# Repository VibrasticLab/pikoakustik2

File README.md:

# Pikoakustik V2

This is audiometri tool project (still in heavy development).
Main chip are STM32F4 and Audio-DAC MAX98357A.

If need previous works, see here: [Pikoakustik](https://github.com/VibrasticLab/pikoakustik)

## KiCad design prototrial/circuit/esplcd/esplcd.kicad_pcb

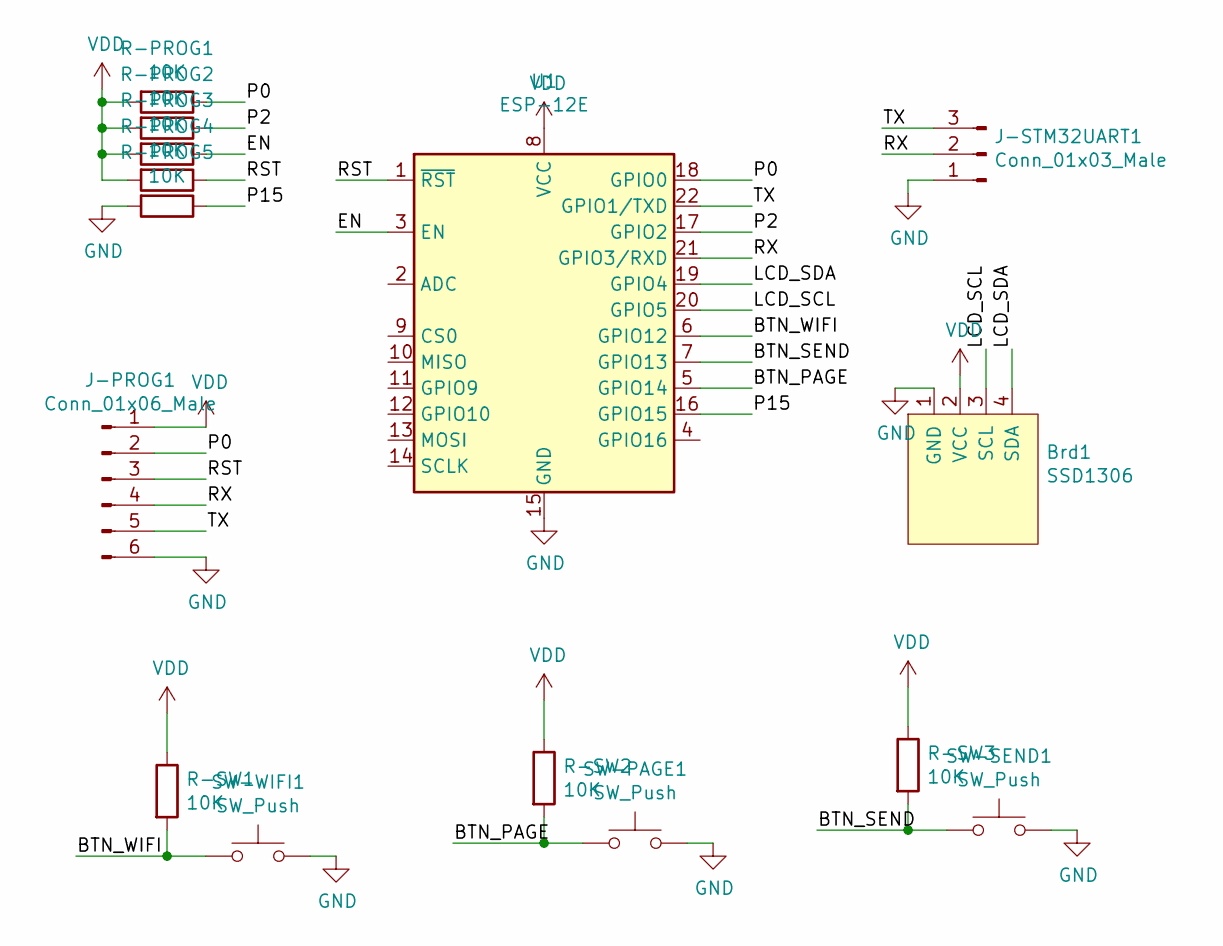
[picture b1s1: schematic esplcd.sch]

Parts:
Brd1: SSD1306; 128x64OLED
J-PROG1: Conn_01x06_Male; PinHeader_1x06_P2.54mm_Vertical
J-STM32UART1: Conn_01x03_Male; Molex_KK-254_AE-6410-03A_1x03_P2.54mm_Vertical
R-PROG1, R-PROG2, R-PROG3, R-PROG4, R-PROG5: 10K; R_0805_2012Metric_Pad1.20x1.40mm_HandSolder
R-SW1, R-SW2, R-SW3: 10K; R_0805_2012Metric_Pad1.20x1.40mm_HandSolder
SW-PAGE1: SW_Push; SW_PUSH_6mm
SW-SEND1: SW_Push; SW_PUSH_6mm
SW-WIFI1: SW_Push; SW_PUSH_6mm
U1: ESP-12E

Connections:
/BTN_PAGE: R-SW2.2, SW-PAGE1.1, U1.5 (GPIO14)
/BTN_SEND: R-SW3.2, SW-SEND1.1, U1.7 (GPIO13)
/BTN_WIFI: R-SW1.2, SW-WIFI1.1, U1.6 (GPIO12)
/EN: R-PROG3.1, U1.3 (EN)
/LCD_SCL: Brd1.3 (SCL), U1.20 (GPIO5)
/LCD_SDA: Brd1.4 (SDA), U1.19 (GPIO4)
/P0: J-PROG1.2, R-PROG1.1, U1.18 (GPIO0)
/P2: R-PROG2.1, U1.17 (GPIO2)
/P15: R-PROG5.1, U1.16 (GPIO15)
/RST: J-PROG1.3, R-PROG4.1, U1.1 (~RST)
/RX: J-PROG1.4, J-STM32UART1.2, U1.21 (GPIO3/RXD)
/TX: J-PROG1.5, J-STM32UART1.3, U1.22 (GPIO1/TXD)
GND: Brd1.1 (GND), J-PROG1.6, J-STM32UART1.1, R-PROG5.2, SW-PAGE1.2, SW-SEND1.2, SW-WIFI1.2, U1.15 (GND)
VDD: Brd1.2 (VCC), J-PROG1.1, R-PROG1.2, R-PROG2.2, R-PROG3.2, R-PROG4.2, R-SW1.1, R-SW2.1, R-SW3.1, U1.8 (VCC)

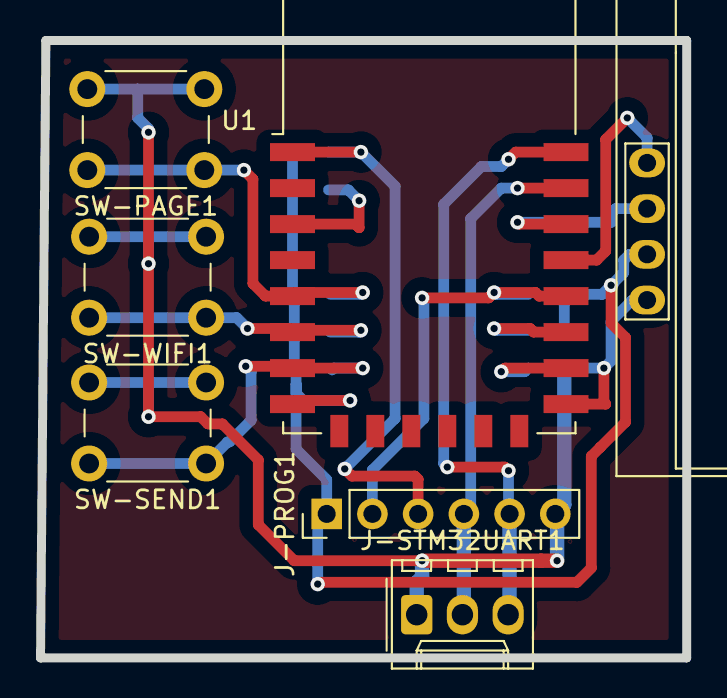
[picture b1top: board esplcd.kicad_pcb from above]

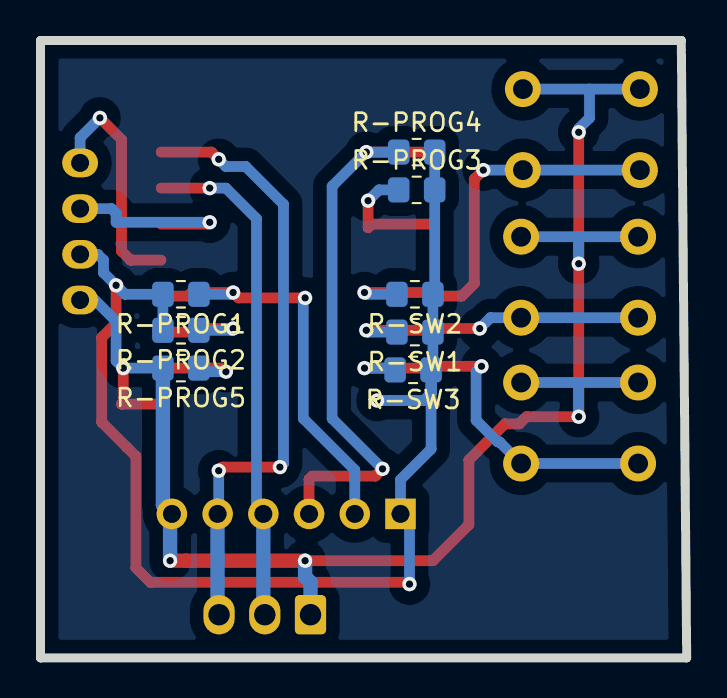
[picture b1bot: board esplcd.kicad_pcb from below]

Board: 2 copper layers, 35.9 x 34.3 mm, 15 parts (8 on the bottom side), 14 nets.

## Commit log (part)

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2022-01-13 working good
2022-01-13 I2C address
2022-01-14 finally working example SH1106 LCD
2022-01-14 basic example ESP8266 OLED
2022-01-14 logo lab
2022-01-15 start working for page home
2022-01-15 Batt Display
2022-01-15 page home draft
2022-01-15 no echo/prompt console
2022-01-21 circuit esplcd proto
2022-01-21 esp lcd draft
2022-01-25 page plot
2022-01-25 send page
2022-01-25 paging jalan
2022-02-02 start reworking on ESP32
2022-02-03 progressing
2022-02-10 progress ESP32
2022-02-11 ambient value
2022-02-12 skematik only
2022-02-14 stm32 part
2022-02-14 multi sheet schematic
2022-02-14 All Part
2022-02-14 Hide Reference Lables
2022-02-14 Still confuse on better looks schematics
2022-02-14 RX/TX resistor
2022-02-15 Mic result seems weird
2022-02-15 I2S 16bit seems working
2022-02-17 ambient dB Max value
2022-02-18 mic buffer as static
2022-02-19 doxygen document
2022-02-19 doxygen
2022-02-23 rework basic schematic into Altium
2022-02-23 Altium seems as fun as KiCAD
2022-02-23 try re-drafting to Altium
2022-02-28 STM32F407 Doc
2022-03-07 update STM32
2022-03-07 Altium Basic
2022-03-07 Altium Basic All
2022-03-08 F303 alternatif
2022-03-08 GPIO
2022-03-15 pin button remap
2022-03-20 interrupt remap
2022-03-23 iot data GET failed
2022-03-23 GET socket run
2022-03-24 send IoT JSON works
2022-03-24 disable all log output
2022-03-24 LCD sending
2022-03-25 ESP32 project files
2022-03-25 use clangd in VSCodium/Vim-CoC only
2022-03-26 qtcreator with no clang code model
2022-03-26 base STM32
2022-03-26 prepare for UART-UART data exchange
2022-03-27 both serial works
2022-03-27 audio re-implement
2022-03-28 trying to UART-UART at 38400
2022-03-28 first UART-UART message flow
2022-03-28 seems CTS/DTS still influence ESP32
2022-03-31 R-GAIN to VDD only
2022-03-31 MMC reimplementation
2022-03-31 tone test command
2022-04-01 EXTI/METRI reimplementation
2022-04-01 progress
2022-04-01 MMC reimplemented
2022-04-01 virtual test freeze
2022-04-01 MMC seem problematic
2022-04-01 Virt Test failed even without MMC
2022-04-01 Drop Test Mode
2022-04-01 MMC is very annoying
2022-04-01 doxygen code browsing
2022-04-01 reimplementation done for STM32F401RE
2022-04-01 Complete JSON failed on server
2022-04-01 ESP32 connect option to STM32
2022-04-02 json string
2022-04-02 android serial interface
2022-04-02 APP reworking
2022-04-02 basic App
2022-04-02 JSON data failed spectacularly
2022-04-02 Flutter serial usb very limited
2022-04-02 update cat routine
2022-04-02 flutter is so baaaaddddd
2022-04-02 drop flutter since usb_serial is not work
2022-04-02 drop tester and replace with iot key
2022-04-02 Qt Data Viewer
2022-04-02 Serial List
2022-04-03 progress Qt interface
2022-04-03 serial OK
2022-04-03 Qt Flist
2022-04-03 Style as Fusion
2022-04-03 Before JSON
2022-04-03 JSON parser for one frequency
2022-04-03 STM32 disable all metri debug message
2022-04-04 MMC file bomb bug
2022-04-04 Thread heap size max at 2048
2022-04-04 different MMC write method
2022-04-04 Test Virt must be connected to CDC Terminal
2022-04-04 Working with some bugs
2022-04-04 full freq
2022-04-04 stm32 program script
2022-04-04 progress Data Viewer
2022-04-04 Json Validate
2022-04-04 Next: Summary
2022-04-05 progress serial Qt
2022-04-05 Qt Next: Summary
2022-04-05 STM32 tone min max
2022-04-05 Qt icons
2022-04-05 serial enable/disable
2022-04-05 minimum feature OK
2022-04-06 stm32 milestone
2022-04-06 Qt Next: Plot tooltip
2022-04-06 Windows alternative icon
2022-04-06 Use imageformats/qsvg.dll for Windows
2022-04-06 QwtPlot tooltip still not found
2022-04-08 try to suppress pop click
2022-04-08 output polynomial model Miniso
2022-04-08 measurement data salvage
2022-04-09 techincal issue
2022-04-16 tone without attenuation
2022-04-19 some improvement
2022-04-20 update tone generation code
2022-04-20 update relay audio
2022-04-20 prepare new redesign
2022-04-20 redesign diagram
2022-04-21 libraries re-path
2022-04-21 power diagram
2022-04-21 Diagram
2022-04-22 laporan latex
2022-04-22 laporan
2022-04-27 update laporan
2022-04-27 Sine form generator
2022-04-27 dokumen
2022-04-27 laporan Xirca 042022
2022-04-27 latex make clean
2022-05-05 New PCB Altium
2022-05-05 remove unused
2022-05-05 update PCB Power
2022-05-06 upate PCB
2022-05-06 update PCB P3
2022-05-06 summary update PCB
2022-05-08 catatan desain
2022-05-13 update PCB
2022-05-28 change scale to 11-1
2022-06-04 Start F303
2022-06-04 start actual instead trial
2022-06-04 start actual on f303rc
2022-06-04 try F303RC USB
2022-06-05 progress tes f303rc
2022-06-05 source tree F303RC and F401RE
2022-06-08 F303RC I2S
2022-06-08 update source tree
2022-06-10 new source tree using ChibiOS/RT 20.3.x
2022-06-10 I2S pin choice for F303RC and F401RE
2022-06-10 MMC SPI changes on 20.3
2022-06-10 SPI MMC working
2022-06-11 progress EXTI
2022-06-12 PAL Callbacks test
2022-06-12 button compileable
2022-06-12 Full implementation Test on F303RC
2022-06-12 RUN mode option
2022-06-12 Can use TRNG on F303RC/F401RE
2022-06-12 Consumer config
2022-06-12 F303RC OK
2022-06-12 some checking
2022-06-12 F401RE SPI MMC failed
2022-06-12 drop previous source tree
2022-06-12 I2S for F401RE freeze
2022-06-12 F303RC PCB is too damaged
2022-06-12 Why ChibiOS/RT so buggy?
2022-06-12 i2sStartExchange freeze on F401RE
2022-06-13 F303RC use 20.3 while F401RE use 17.6
2022-06-13 Scaling Frequency
2022-06-13 improve audio frequency
2022-06-13 Design Notes
2022-06-15 Re-Check codes
2022-06-15 F401RE ChibiOS/RT 20.3.x still freeze
2022-06-15 guarding session start if MMC fail
2022-06-16 Debugging F401RE on 20.3.x didnt found anything
2022-06-16 Long File Name support
2022-06-21 Improving the MMC
2022-06-21 improve MMC
2022-06-22 MMC disk formatting
2022-06-22 MMC disk formatting not work
2022-06-22 update Altium design
2022-06-29 ESP32 rewriting
2022-06-29 ESP32 UART0 rewriting
2022-06-29 use Silent UART
2022-06-29 UART0 OK
2022-06-29 ESP32 use UART1
2022-06-29 Shell got unrecognized command
2022-06-29 ESP32 UART-1 supressed messages works
2022-06-30 ESP32 rewrite progress
2022-07-05 progress PCB
2022-07-05 ESP32 WiFi
2022-07-07 try stereo array
2022-07-07 drop WEIRD_SINE array
2022-07-07 Stereo Array and Drop Weird Sine
2022-07-07 progress di Xirca
2022-07-07 new line on ESP32 cmds
2022-07-07 Chip alternatives
2022-07-08 Home Page Display ESP32
2022-07-08 prepare for F303RB
2022-07-08 Adjust STM32 I2S DMA array size
2022-07-08 Adjust STM32 I2S DMA array
2022-07-08 ADC ESP32
2022-07-27 STM32 Left/Right relay pin
2022-07-27 Progress P3 adjustment
2022-07-28 progress status exchange
2022-07-28 Progress Xirca
2022-07-28 IO Status Ready
2022-07-28 STM32 IO Status
2022-07-28 Default Channel as Left
2022-07-28 ESP32 Flash script
2022-07-28 Some Nutes
2022-07-28 Try ADC Battery on ESP32
2022-07-29 ESP32 UART Options
2022-07-29 ESP32 read adc battery
2022-07-29 ESP32 Battery ADC
2022-07-29 Page Button
2022-07-29 Casing Notes
2022-07-29 Re-Check UART on ESP32
2022-08-23 Improve for demo
2022-08-23 Example Datasheet Template
2022-08-23 Spec Doc
2022-08-23 Sleep time
2022-08-24 Spec DOcument
2022-09-05 More Restrict Ruleset
2022-09-06 More Restrict
2022-09-06 Faster
2022-09-06 Remove Files
2022-09-13 Revert back to P2 method
2022-09-19 Dokumen improvisasi
2022-09-22 Dokumen Improvemen
2022-09-22 Dokumen Improvement
2022-09-22 Dokumen imrprove
2022-10-02 ESP32 HTTPD
2022-10-02 ESP32 Main thread need 10ms delay
2022-10-02 Improving ESP32 (Wifi AP Interface)
2022-10-02 ESP32 TestData
2022-10-02 WiFi AP start on Button Action X
2022-10-02 remove unnecessary headers
2022-10-03 MicGet follow CMD macro
2022-10-03 Start building data exchange STM32-ESP32
2022-10-10 Dokumen improve
2022-10-10 Dokumen Improve Casing
2022-10-30 Dokumen Gagal Impor
2022-11-03 Edit things
2022-11-04 ESP32 Audiometri run progress
2022-11-04 STM32 Audiometri Progress
2022-11-04 Frequency Progress Implemented
2022-11-09 Dokumen Uji Homogen
2022-11-09 Uji Homogen
2022-11-10 STM32 use only record at the end method
2022-11-10 Update Manual Buffer Saving
2022-11-10 Serial ESP32 to STM32 failed
2022-11-14 STM32 UART RX error
2022-11-18 Python Data Viewer
2022-11-18 Python Dataviewer
2022-11-19 Dataviewer contoh valid JSON (RFC 8259)
2022-11-19 start working on JSON handling
2022-11-21 Dataviewer using PyQtGraph
2022-11-21 JSON PyQtGraph
2022-11-21 Progress Interface Python
2022-11-22 Progress Dataviewer
2022-11-22 Add Matplotlib Plot
2022-11-22 Drop PyQTGraph
2022-11-22 Done
2022-11-22 Install Tutorial
2022-11-22 Tutorial
2022-11-22 Tutorial Done
2022-11-22 Data Viewer GUI Done
2022-11-23 Workaround Unsaved result Bug
2022-11-23 Workaround Wrong Answer Choice Bug
2022-11-23 STM32 buffer save always overwrite
2022-11-23 GCC Optimization use O2
2022-11-24 Plot Dataviewer can close prev window
2022-11-25 Buffer dump using same filename
2022-11-25 Modify File Managament on Audiometri session
2022-11-25 Buffer Order File on STM32 Audiometri
2022-11-29 JSON Save Improve
2022-11-30 MMC Saving USB Message
2022-12-02 Improve Wrong Answers
2022-12-02 Bugfixes Memory Buffer
2022-12-06 STM32 disable Log by default
2023-01-11 Tryto solve button input bug
2023-01-12 Revisi tombol STM32
2023-01-23 New Calib
2023-01-24 Audiogram Plot
2023-01-24 HL Plot
2023-01-24 Update Plot Data
2023-01-31 P3 in KiCAD
2023-01-31 P3 in KiCAD Schematic
2023-02-06 Update di Xirca
2023-02-07 dokumen blueprint
2023-02-07 update blueprint
2023-02-07 update on blueprint
2023-02-07 Update Stiker Casing
2023-02-07 Update Casing
2023-02-07 Casing Stiker
2023-02-07 Stiker Casing
2023-02-07 update manual book
2023-02-08 Revisi P3
2023-02-11 update on risk management
2023-02-13 Moms as LaTeX
2023-02-13 MoM LaTeX
2023-03-07 Panduan Ujicoba
2023-03-08 Uji EARS
2023-03-08 Panduan EARS
2023-03-13 Uji KAN
2023-03-15 Komparasi EARS SLM
2023-03-15 Ignore video
2023-04-01 Update Notes
2023-04-07 PTA view page
2023-04-07 STM32 UART Shell not work
2023-04-07 Resolved conflict on UART1 pins
2023-04-13 Start PTA Viewer
2023-05-09 Update ESP32 Progs
2023-05-09 STM32 use QtCreator
2023-05-09 Start Working on Calibration routine
2023-05-10 PTA implementation
2023-05-10 JSON in C
2023-05-10 Not Enough space on STM32 for JSMN Parser
2023-05-10 JSON Parser on ESP32
2023-05-10 update on manual book
2023-05-11 JSON use JSMN with lower Token size
2023-05-11 PTA on STM32
2023-05-11 STM32 Console callback documentation
2023-05-11 PTA Upper Limit Array
2023-05-11 Temporarily disable unused features
2023-05-11 Update ESP32
2023-05-11 ESP32 PTA
2023-05-12 PTA show file Number
2023-05-12 PTA Reset
2023-05-13 update on management risk dokumen
2023-05-13 Dokumentasi GQI
2023-05-14 update on risk management book
2023-05-15 Disable strtok() parse method
2023-05-15 Improve PTA function
2023-05-15 Nont on PTA command
2023-05-15 Fix dual PTA command on UART
2023-05-15 Berita Acara GQI
2023-05-15 final draft on manual and risk management book
2023-05-28 manual uji prototipe
2023-05-29 update on manual procedure
2023-05-30 olah data headphone
2023-05-31 Benerin Code Block
2023-05-31 Update Dokumen KP
2023-05-31 KP nya Ammar
2023-06-02 3DIO Setup
2023-06-05 Metode Ruang Dengung
2023-07-06 Add 125Hz to Test Console
2023-07-08 Laporan Kegiatan
2023-07-09 Dokumen Kalibrasi Kuping
2023-07-09 Dokumen Kalibrasi Ruang Dengung
2023-07-09 report template
2023-07-09 update on images
2023-07-09 update on report activity document
2023-07-10 Koleksi Data July 2023
2023-07-10 Extract Data Python
2023-07-10 Python Extract Data
2023-07-10 Python Extract Data OK
2023-07-10 Modify Out Name
2023-07-11 Laporan Self Test
2023-07-11 update on data records
2023-07-12 Update Dokumen Self-Test ITB sebelum ke BPFK
2023-07-12 Hide all KEMAR testing
2023-07-12 Prepare document
2023-07-22 Interface BPFK
2023-07-22 BPFK Interface
2023-07-23 Prepare to Windows
